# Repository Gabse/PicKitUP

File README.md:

# PicKitUP

AVR & SAM Adapter for Pickit4/SNAP 

=
Just a simple adapter board to connect most common AVR and SAM ICSP Ports to the Microchip Pickit4/SNAP Programmer

=
If you Like this Project you can donate to the KiCad Project :

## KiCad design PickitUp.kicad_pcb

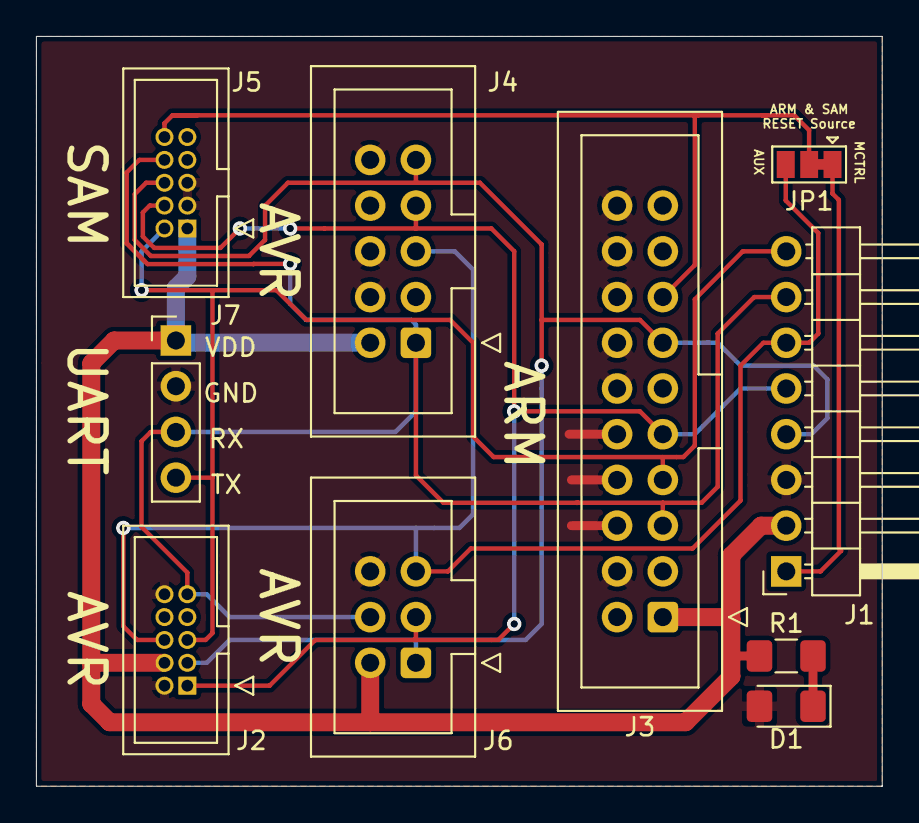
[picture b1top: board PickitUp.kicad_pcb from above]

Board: 2 copper layers, 47.0 x 41.7 mm, 10 parts (0 on the bottom side), 10 nets.

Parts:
D1: LED; LED_1206_3216Metric_Pad1.42x1.75mm_HandSolder
J1: PicKit_Connector; PinHeader_1x08_P2.54mm_Horizontal_Inverse
J2: AVR-JTAG-10; SHF-105-01-L-D-TH
J3: ARM_JTAG_20; IDC-Header_2x10_P2.54mm_Vertical
J4: AVR-ISP-10; IDC-Header_2x05_P2.54mm_Vertical
J5: ARM_JTAG_10; SHF-105-01-L-D-TH
J6: AVR-ISP-6; IDC-Header_2x03_P2.54mm_Vertical
J7: UART; PinHeader_1x04_P2.54mm_Vertical
JP1: RESET; SolderJumper-3_P1.3mm_Bridged12_Pad1.0x1.5mm
R1: 1k; R_1206_3216Metric_Pad1.42x1.75mm_HandSolder

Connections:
/AUX: J1.6, J2.6, J4.5, J6.5, JP1.3
/GND: D1.2, J1.3, J2.2, J2.10, J3.4, J3.6, J3.8, J3.10, J3.12, J3.14, J3.16, J3.18, J3.20, J4.4, J4.6, J4.8, J4.10, J5.3, J5.5, J6.6, J7.2
/MCLR: J1.1, JP1.1
/PGC: J1.5, J2.1, J3.9, J4.7, J5.4, J6.3
/PGD: J1.4, J2.3, J3.13, J4.9, J5.6, J6.1
/RESET: J3.15, J5.10, JP1.2
/TDI: J1.7, J2.9, J3.5, J4.1, J5.8, J6.4, J7.3
/TMS: J1.8, J2.5, J3.7, J5.2, J7.4
/VDD: J1.2, J2.4, J3.1, J4.2, J5.1, J6.2, J7.1, R1.1
unnamed: D1.1, R1.2

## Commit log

2020-11-29 Version 1
    Commit of the first version

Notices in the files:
PickitUp.kicad_pcb:
GPL
